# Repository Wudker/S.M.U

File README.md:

# S.M.U. – Custom RLC Component Meter

S.M.U. is a portable RLC meter based on the Raspberry Pi Pico, developed for testing coils and passive components during electronics prototyping. Resistance is measured using a voltage divider, capacitance through RC discharge timing to approximately 37% of the initial voltage, and inductance through LC resonance and frequency analysis. Custom measurement algorithms and automatic range switching process the signals, while an SSD1306 OLED presents the results. The device combines analog measurement circuits, embedded software, a custom PCB and Li-Ion power supply in a single enclosure.

## Technologies

`Raspberry Pi Pico` `C/C++` `ADC measurements` `RC time constant` `LC resonance` `LM339 comparator` `SSD1306 OLED` `Custom PCB` `Li-Ion battery`

## Usage and development status

Select resistance, capacitance or inductance mode, place the unpowered component in the measurement connector and start the measurement. Capacitors should always be fully discharged before being connected. The prototype has been built and tested; future improvements include increased accuracy, more reliable auto-ranging, improved stability and a redesigned analog front-end.

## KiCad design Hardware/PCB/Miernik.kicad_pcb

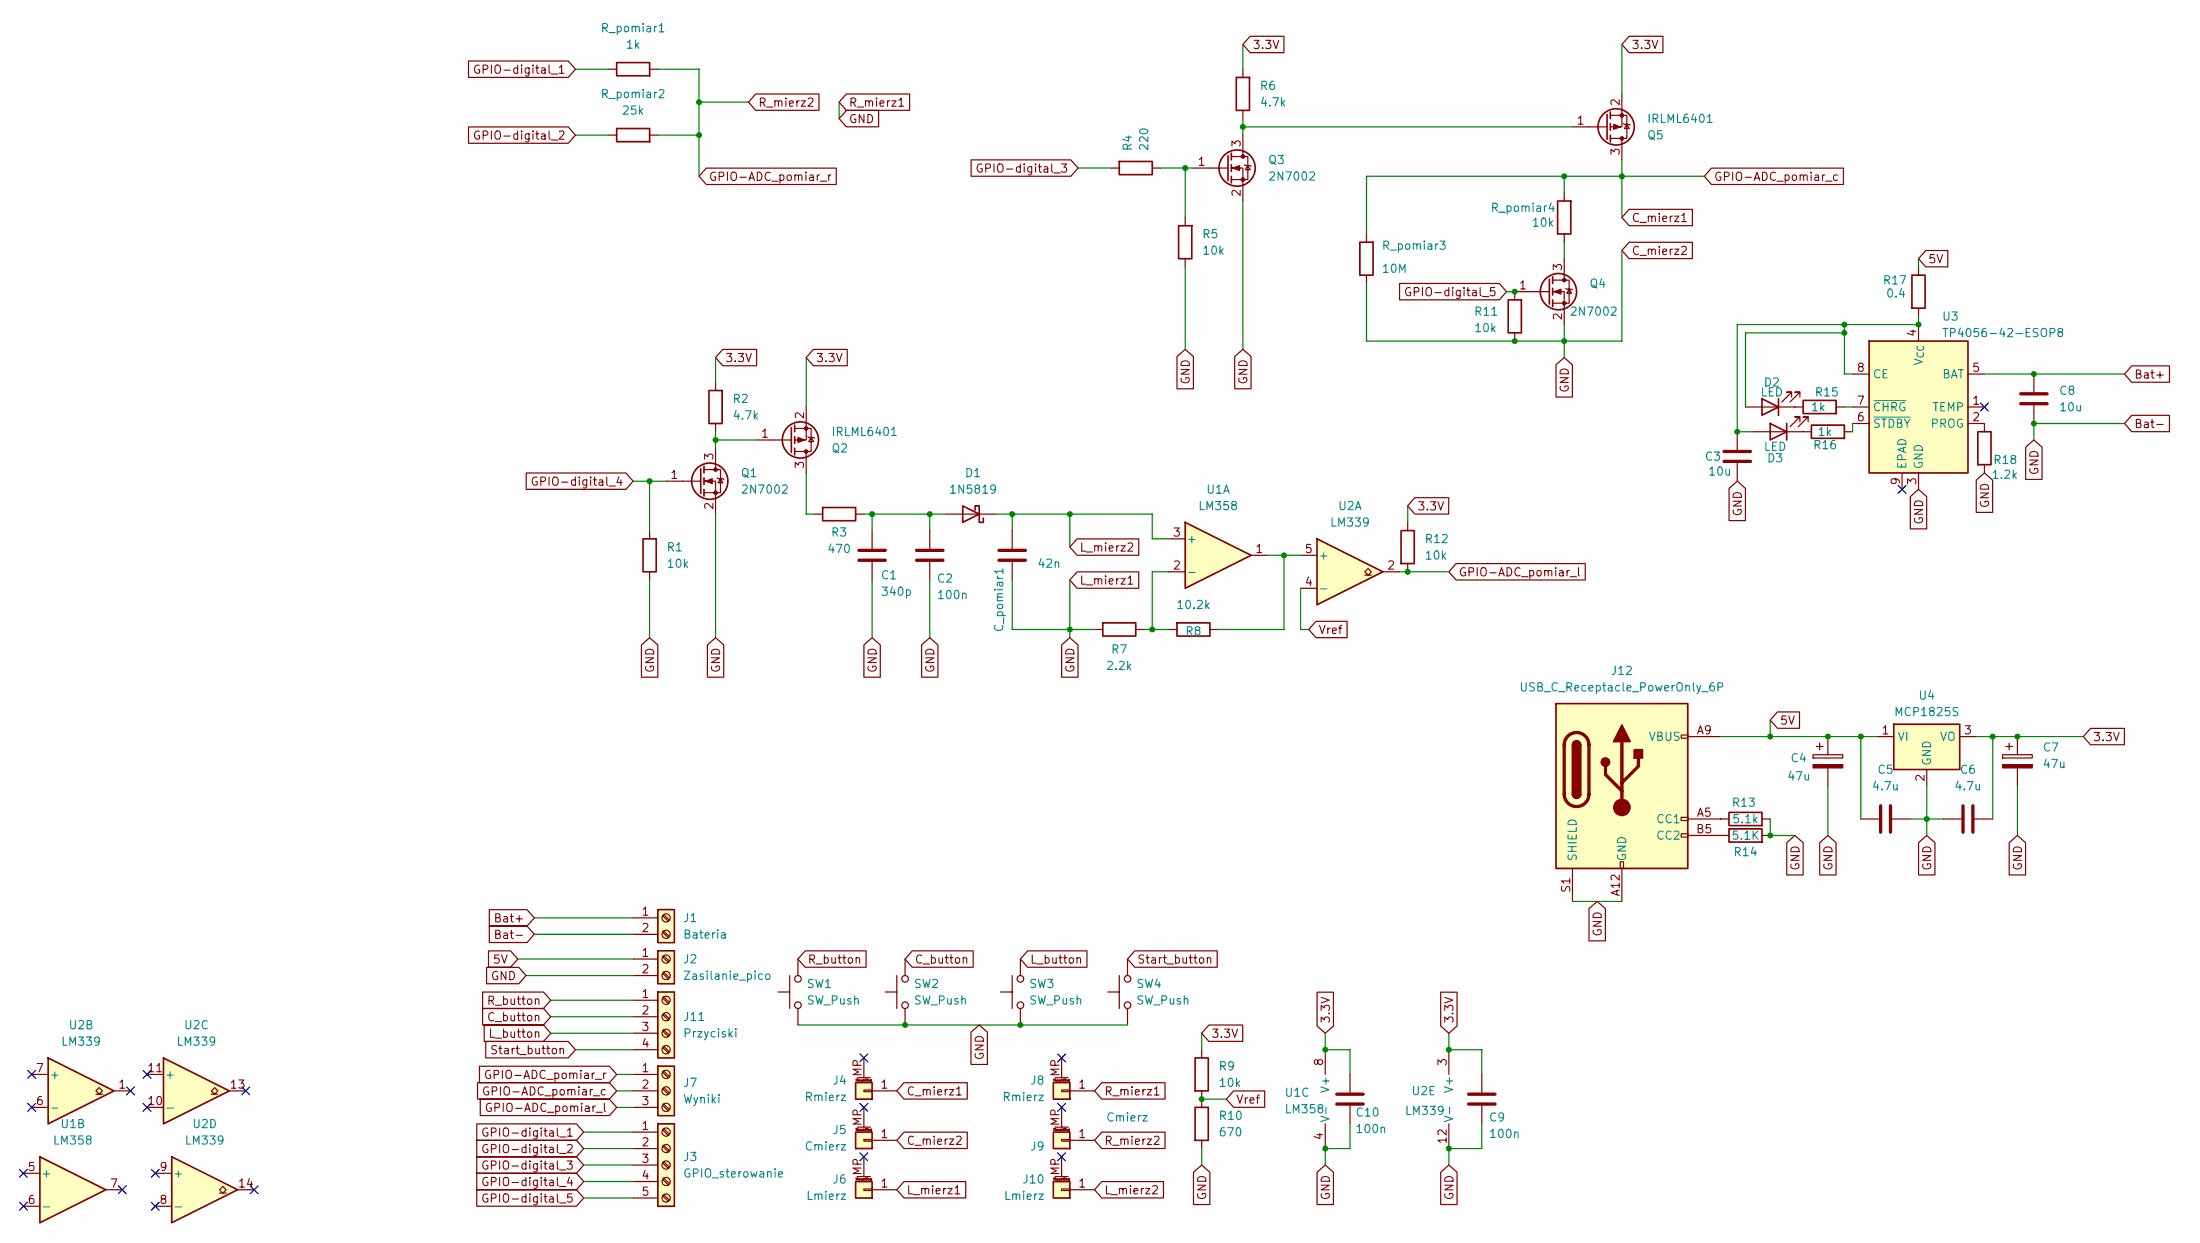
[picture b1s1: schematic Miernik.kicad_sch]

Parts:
C1: 340p; C_1206_3216Metric
C2, C9, C10: 100n; C_1206_3216Metric
C3, C8: 10u; C_1206_3216Metric
C4, C7: 47u; C_1206_3216Metric
C5, C6: 4.7u; C_1206_3216Metric
C_pomiar1: 42n; C_Axial_L12.0mm_D6.5mm_P15.00mm_Horizontal
D1: 1N5819; D_DO-41_SOD81_P10.16mm_Horizontal
D2, D3: LED; LED_1206_3216Metric
J1: Bateria; TerminalBlock_Phoenix_MPT-0,5-2-2.54_1x02_P2.54mm_Horizontal
J2: Zasilanie_pico; TerminalBlock_Phoenix_MPT-0,5-2-2.54_1x02_P2.54mm_Horizontal
J3: GPIO_sterowanie; TerminalBlock_Phoenix_MPT-0,5-5-2.54_1x05_P2.54mm_Horizontal
J4, J8: Rmierz; PinSocket_1x01_P2.00mm_Vertical
J5, J9: Cmierz; PinSocket_1x01_P2.00mm_Vertical
J6, J10: Lmierz; PinSocket_1x01_P2.00mm_Vertical
J7: Wyniki; TerminalBlock_Phoenix_MPT-0,5-3-2.54_1x03_P2.54mm_Horizontal
J11: Przyciski; TerminalBlock_Phoenix_MPT-0,5-4-2.54_1x04_P2.54mm_Horizontal
J12: USB_C_Receptacle_PowerOnly_6P; USB_C_Receptacle_GCT_USB4125-xx-x_6P_TopMnt_Horizontal
Q1, Q3, Q4: 2N7002; SOT-23
Q2, Q5: IRLML6401; SOT-23
R1, R5, R9, R11, R12: 10k; R_1206_3216Metric
R2, R6: 4.7k; R_1206_3216Metric
R3: 470; R_1206_3216Metric
R4: 220; R_1206_3216Metric
R7: 2.2k; R_1206_3216Metric
R8: 10.2k; R_1206_3216Metric
R10: 670; R_1206_3216Metric
R13: 5.1k; R_1206_3216Metric
R14: 5.1K; R_1206_3216Metric
R15, R16: 1k; R_1206_3216Metric
R17: 0.4; R_1206_3216Metric
R18: 1.2k; R_1206_3216Metric
R_pomiar1: 1k; R_1206_3216Metric
R_pomiar2: 25k; R_1206_3216Metric
R_pomiar3: 10M; R_1206_3216Metric
R_pomiar4: 10k; R_1206_3216Metric
SW1, SW2, SW3, SW4: SW_Push; SW_PUSH_6mm_H8mm
U1: LM358; Infineon_PG-DSO-8-24_4x5mm
U2: LM339; SO-14_3.9x8.65mm_P1.27mm
U3: TP4056-42-ESOP8; SOIC-8-1EP_3.9x4.9mm_P1.27mm_EP2.41x3.3mm_ThermalVias
U4: MCP1825S; SOT-223-3_TabPin2

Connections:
3.3V: C6.2, C7.1, C9.1, C10.1, Q2.2 (S), Q5.2 (S), R2.2, R6.2, R9.1, R12.1, U1.8 (V+), U2.3 (V+), U4.3 (VO)
5V: C4.1, C5.1, J2.1, J12.A9 (VBUS), J12.B9 (VBUS), R17.1, U4.1 (VI)
Bat+: C8.2, J1.1, U3.5 (BAT)
C_button: J11.2, SW2.2
C_mierz1: J4.1, J7.2, Q5.3 (D), R_pomiar3.2, R_pomiar4.2
GND: C1.2, C2.2, C3.1, C4.2, C5.2, C6.1, C7.2, C8.1, C9.2, C10.2, C_pomiar1.2, J1.2, J2.2, J5.1, J6.1, J8.1, J12.A12 (GND), J12.B12 (GND), J12.S1 (SHIELD), Q1.2 (S), Q3.2 (S), Q4.2 (S), R1.1, R5.1, R7.2, R10.2, R11.1, R13.2, R14.2, R18.2, R_pomiar3.1, SW1.1, SW2.1, SW3.1, SW4.1, U1.4 (V-), U2.12 (V-), U3.3 (GND), U4.2 (GND)
GPIO-ADC_pomiar_l: J7.3, R12.2, U2.2
GPIO-ADC_pomiar_r: J7.1, J9.1, R_pomiar1.2, R_pomiar2.2
GPIO-digital_1: J3.1, R_pomiar1.1
GPIO-digital_2: J3.2, R_pomiar2.1
GPIO-digital_3: J3.3, R4.2
GPIO-digital_4: J3.4, Q1.1 (G), R1.2
GPIO-digital_5: J3.5, Q4.1 (G), R11.2
L_button: J11.3, SW3.2
L_mierz2: C_pomiar1.1, D1.1 (K), J10.1, U1.3 (+)
unnamed: C1.1, C2.1, D1.2 (A), R3.1
unnamed: C3.2, D2.2 (A), D3.2 (A), R17.2, U3.4 (V_{CC}), U3.8 (CE)
unnamed: D2.1 (K), R15.1
unnamed: D3.1 (K), R16.1
unnamed: J12.A5 (CC1), R13.1
unnamed: J12.B5 (CC2), R14.1
unnamed: Q1.3 (D), Q2.1 (G), R2.1
unnamed: Q2.3 (D), R3.2
unnamed: Q3.3 (D), Q5.1 (G), R6.1
unnamed: Q3.1 (G), R4.1, R5.2
unnamed: Q4.3 (D), R_pomiar4.1
unnamed: R7.1, R8.2, U1.2 (-)
unnamed: R8.1, U1.1, U2.5 (+)
unnamed: R18.1, U3.2 (PROG)
unnamed: R15.2, U3.7 (~CHRG)
unnamed: R16.2, U3.6 (~STDBY)
R_button: J11.1, SW1.2
Start_button: J11.4, SW4.2
Vref: R9.2, R10.1, U2.4 (-)

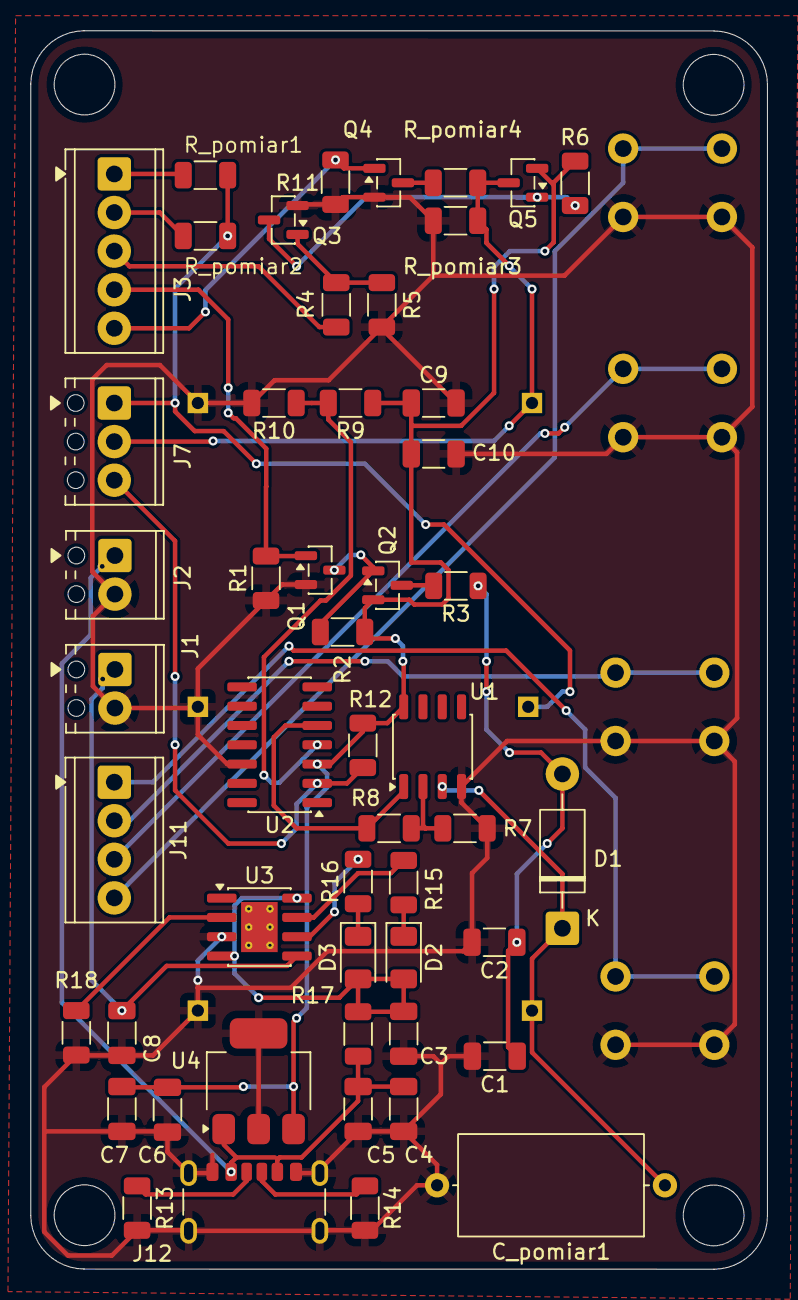
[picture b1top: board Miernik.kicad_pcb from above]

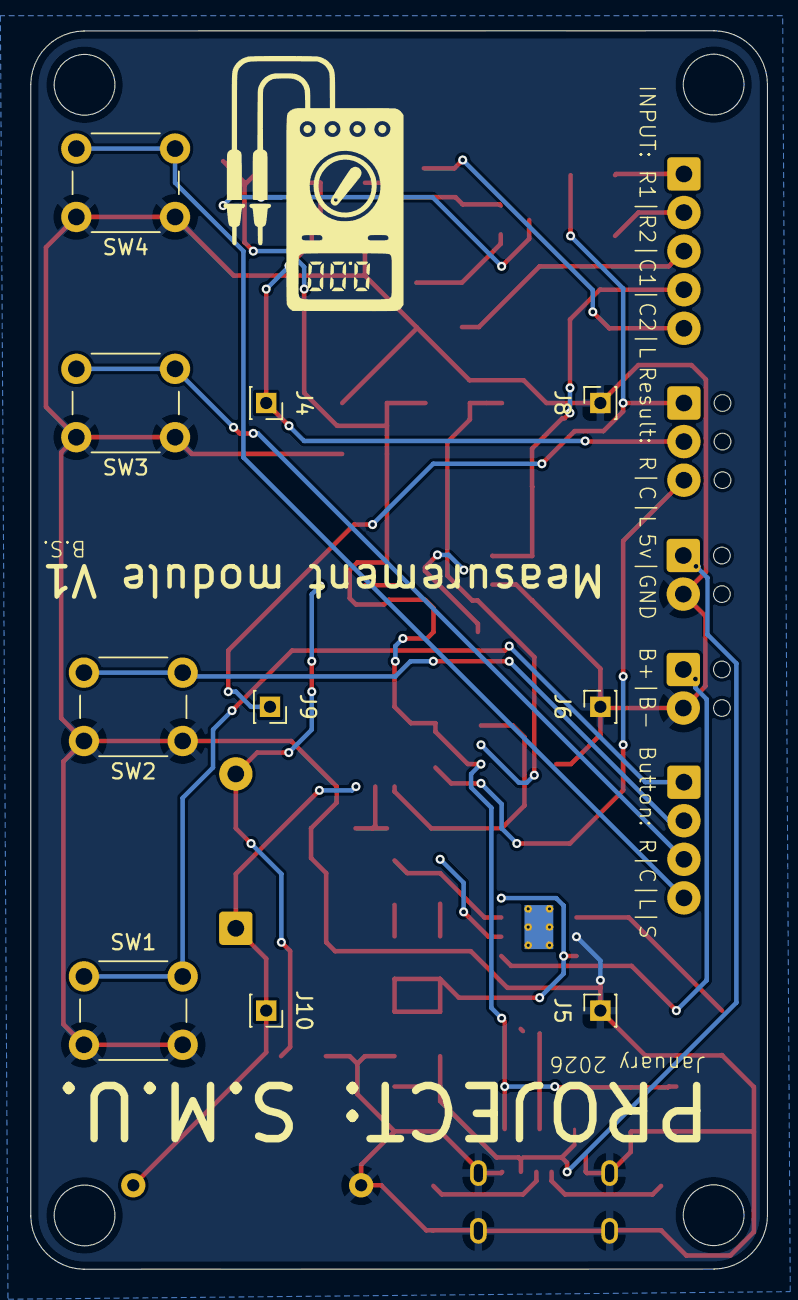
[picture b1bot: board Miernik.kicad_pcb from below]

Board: 2 copper layers, 48.5 x 81.5 mm, 61 parts (10 on the bottom side), 34 nets.

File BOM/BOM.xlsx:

Nazwa | Wartośc | Footprint | Link | Link
C1 | 340p | Capacitor_SMD:C_1206_3216Metric | TAK | https://www.tme.eu/pl/details/c1206c331j5gac/kondensatory-ml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
> C2, C9, C10 | 100n | Capacitor_SMD:C_1206_3216Metric | TAK | https://www.tme.eu/pl/details/cl31b104kbcnnnc/kondensatory-m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
> C3, C8 | 10u | Capacitor_SMD:C_1206_3216Metric | TAK | https://www.tme.eu/pl/details/cl31b106kbhnnne/kondensatory-m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
> C4, C7 | 47u | Capacitor_SMD:C_1206_3216Metric | TAK | https://www.tme.eu/pl/details/cl31a476mphnnne/kondensatory-m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
> C5, C6 | 4.7u | Capacitor_SMD:C_1206_3216Metric | TAK | https://www.tme.eu/pl/details/cl31b475kbhnnne/kondensatory-m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
C_pomiar1 | 42n | Capacitor_THT:C_Axial_L12.0mm_D6.5mm_P15.00mm_Horizontal | TAK | https://www.tme.eu/pl/details/mkp2-47n_250-r-5/kondensatory-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
D1 | 1N5819 | Diode_THT:D_DO-41_SOD81_P10.16mm_Horizontal | TAK | https://www.tme.eu/pl/details/1n5819-dio/diody-schottky-tht/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
> D2, D3 | LED | LED_SMD:LED_1206_3216Metric | TAK | https://www.tme.eu/pl/details/of-smd3216r/diody-led-smd-kolo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
J1 | Bateria | TerminalBlock_Phoenix:TerminalBlock_Phoenix_MPT-0,5-2-2.54_1x02_P2.54mm_Horizon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 | TAK | https://botland.com.pl/zlacza-ark/9443-zlacze-ark-raster-254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
J2 | Zasilanie_pico | TerminalBlock_Phoenix:TerminalBlock_Phoenix_MPT-0,5-2-2.54_1x02_P2.54mm_Horizon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 | TAK | https://botland.com.pl/zlacza-ark/9443-zlacze-ark-raster-254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
J3 | GPIO_sterowanie | TerminalBlock_Phoenix:TerminalBlock_Phoenix_MPT-0,5-5-2.54_1x05_P2.54mm_Horizon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 | TAK | łączysz 2+3 itp
> J4, J8 | Rmierz | Connector_PinSocket_2.00mm:PinSocket_1x01_P2.00mm_Vertical | TAK | https://www.tme.eu/pl/details/fci-76357-401/zlacza-sygnalowe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
> J5, J9 | Cmierz | Connector_PinSocket_2.00mm:PinSocket_1x01_P2.00mm_Vertical | TAK | https://www.tme.eu/pl/details/nsr-01/listwy-i-gniazda-kolkow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
> J6, J10 | Lmierz | Connector_PinSocket_2.00mm:PinSocket_1x01_P2.00mm_Vertical | TAK | https://www.tme.eu/pl/details/zl307-1x1/listwy-i-gniazda-kol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
J7 | Wyniki | TerminalBlock_Phoenix:TerminalBlock_Phoenix_MPT-0,5-3-2.54_1x03_P2.54mm_Horizon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 | TAK | https://botland.com.pl/zlacza-ark/9444-zlacze-ark-raster-254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
J11 | Przyciski | TerminalBlock_Phoenix:TerminalBlock_Phoenix_MPT-0,5-4-2.54_1x04_P2.54mm_Horizon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 | TAK | 2+2
J12 | USB_C_Receptacle_PowerOnly_6P | Connector_USB:USB_C_Receptacle_GCT_USB4125-xx-x_6P_TopMnt_Horizontal | TAK | https://www.tme.eu/pl/details/usb4105-gf-a/zlacza-usb-i-ieee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
> Q1, Q3, Q4 | 2N7002 | Package_TO_SOT_SMD:SOT-23 | TAK | https://www.tme.eu/pl/details/2n7002-lge/tranzystory-z-kanal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
> Q2, Q5 | IRLML6401 | Package_TO_SOT_SMD:SOT-23 | TAK | https://www.tme.eu/pl/details/irlml6401trpbf/tranzystory-z-k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
> R1, R5, R9, R11, R12, R_pomiar4 | 10k | Resistor_SMD:R_1206_3216Metric | TAK | https://www.tme.eu/pl/details/ar1206-10k-0.1%25/rezystory-sm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
> R2, R6 | 4.7k | Resistor_SMD:R_1206_3216Metric | TAK | https://www.tme.eu/pl/details/rc1206fr-074k7/rezystory-smd/y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
R3 | 470 | Resistor_SMD:R_1206_3216Metric | TAK | https://www.tme.eu/pl/details/rc1206fr-07470r/rezystory-smd/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
R4 | 220 | Resistor_SMD:R_1206_3216Metric | TAK | https://www.tme.eu/pl/details/crcw1206220rfktabc/rezystory-s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
R7 | 2.2k | Resistor_SMD:R_1206_3216Metric | TAK | https://www.tme.eu/pl/details/rc1206fr-072k2/rezystory-smd/y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
R8 | 10.2k | Resistor_SMD:R_1206_3216Metric | TAK | https://www.tme.eu/pl/details/ar1206-10k2-0.1%25/rezystory-s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
R10 | 670 | Resistor_SMD:R_1206_3216Metric | TAK | https://www.tme.eu/pl/details/rc1206jr-07680r/rezystory-smd/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
R13,R14 | 5.1k | Resistor_SMD:R_1206_3216Metric | TAK | https://www.tme.eu/pl/details/rc1206fr-075r1/rezystory-smd/y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
> R15, R16, R_pomiar1 | 1k | Resistor_SMD:R_1206_3216Metric | TAK | https://www.tme.eu/pl/details/ar1206-1k-0.1%25/rezystory-smd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
R17 | 0.4 | Resistor_SMD:R_1206_3216Metric | TAK | https://www.tme.eu/pl/details/mbr1206b5fr040s/rezystory-smd/wayon/
R18 | 1.2k | Resistor_SMD:R_1206_3216Metric | TAK | https://www.tme.eu/pl/details/rc1206fr-071k2/rezystory-smd/y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
R_pomiar2 | 25k | Resistor_SMD:R_1206_3216Metric | TAK | https://www.tme.eu/pl/details/ar1206-24k9-0.1%25/rezystory-s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
R_pomiar3 | 10M | Resistor_SMD:R_1206_3216Metric | TAK | https://www.tme.eu/pl/details/rc1206fr-0710ml/rezystory-smd/yageo/
> SW1-SW4 | SW_Push | Button_Switch_THT:SW_PUSH_6mm_H8mm | TAK | mam
U1 | LM358 | Package_SO:Infineon_PG-DSO-8-24_4x5mm | TAK | https://www.tme.eu/pl/details/lm358dt/wzmacniacze-operacyjne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
U2 | LM339 | Package_SO:SO-14_3.9x8.65mm_P1.27mm | TAK | https://www.tme.eu/pl/details/lm339dt/komparatory-smd/stmicr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
U3 | TP4056-42-ESOP8 | Package_SO:SOIC-8-1EP_3.9x4.9mm_P1.27mm_EP2.41x3.3mm_ThermalVias | TAK | https://superelektronika.pl/pl/ce/284471649-tp4056-ladowarka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
U4 | MCP1825S | Package_TO_SOT_SMD:SOT-223-3_TabPin2 | TAK | https://www.tme.eu/pl/details/mcp1825s-3302e_db/stabilizator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
https://allegro.pl/oferta/zestaw-wtykow-kolkowych-310-sztuk-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
https://botland.com.pl/akumulatory-li-pol-1s-37v/15627-akumu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
https://botland.com.pl/akumulatory-li-pol-1s-37v/15604-akumu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
https://botland.com.pl/akumulatory-li-pol-1s-37v/15616-akumu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

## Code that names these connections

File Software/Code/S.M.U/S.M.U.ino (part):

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int wynik_pomiaru_C = A0;
int wynik_pomiaru_L = 2;  

int R_button      = 17; 
int C_button      = 16;
int L_button      = 19;
int start         = 18;

// ========================= OLED helpers =========================
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  pinMode(wynik_pomiaru_R, INPUT);
  pinMode(wynik_pomiaru_C, INPUT);
  pinMode(wynik_pomiaru_L, INPUT);
  pinMode(R_button, INPUT_PULLUP);
  pinMode(C_button, INPUT_PULLUP);
  pinMode(L_button, INPUT_PULLUP);
  pinMode(start,    INPUT_PULLUP);

  pinMode(Led_power_on, OUTPUT);
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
